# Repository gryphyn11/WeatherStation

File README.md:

# WeatherStation
A weather station powered by a Raspberry Pi front end, and MSP430 series microcontroller back end.

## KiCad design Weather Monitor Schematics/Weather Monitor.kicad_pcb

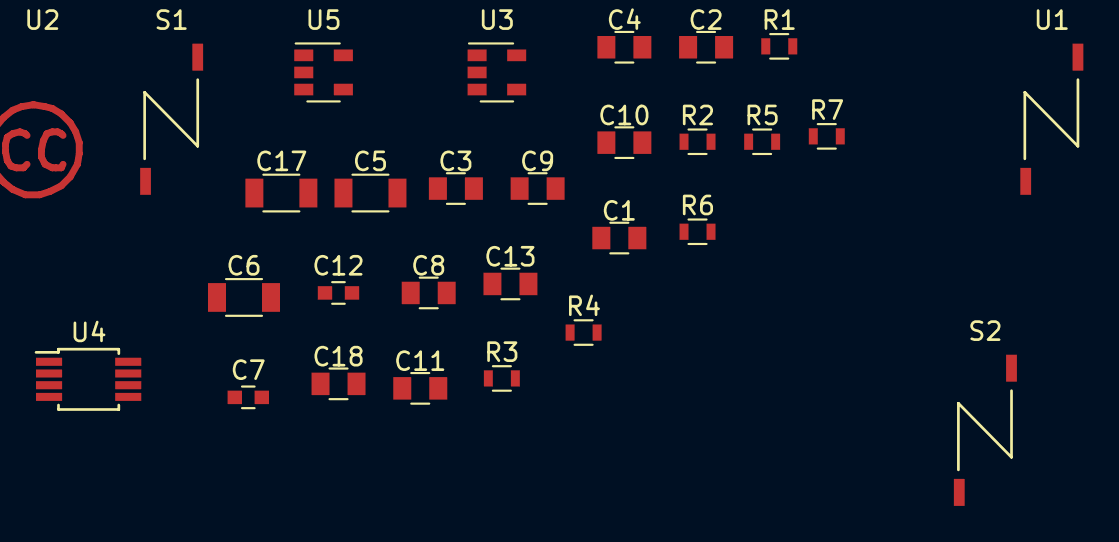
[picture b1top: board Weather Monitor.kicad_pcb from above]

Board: 2 copper layers, 29 parts (0 on the bottom side), 11 nets, no tracks yet.

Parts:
C1, C2, C9, C13: 1.0uF; C_0805
C3, C4, C10, C11: 0.1uF; C_0805
C5, C17: 4.7uF; C_1206
C6: 100nF; C_1206
C7, C12: 0.01uF; C_0603
C8, C18: 2.2uF; C_0805
R1, R2, R3, R4, R5, R6, R7: 4.7k; R_0603
S1, S2: HDC1010; Neosid_Air-Coil_SML_1turn_HDM0131A
U1: MSP430F5659IZQW; Neosid_Air-Coil_SML_1turn_HDM0131A
U2: LPS25HB; Symbol_CreativeCommons_CopperTop_Type2_Small
U3: LP2985-5.0; SOT-23-5
U4: MCP9803_MSOP; MSOP-8_3x3mm_Pitch0.65mm
U5: LP2985-3.3; SOT-23-5

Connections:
/T_P_H_Breakout/SCL_TPH: R7.2, U4.2
/T_P_H_Breakout/SDA_TPH: R6.2, U4.1
/T_P_H_Breakout/TPH_3.3V: C1.2, C3.2, C5.2, C6.1, C11.1, C13.1, C17.1, C18.1, R1.1, R6.1, R7.1, U4.8, U5.5
/T_P_H_Breakout/TPH_5.0V: C8.1, C9.1, C10.1, U3.5, U5.1
/T_P_H_Breakout/TPH_GND: C1.1, C2.2, C3.1, C4.2, C5.1, C6.2, C7.2, C8.2, C9.2, C10.2, C11.2, C12.2, C13.2, C17.2, C18.2, R2.2, R4.1, U3.2, U4.4, U5.2
/T_P_H_Breakout/V_IN_TPH: C2.1, C4.1, U3.1
unnamed: C7.1, U3.4
unnamed: C12.1, U5.4
unnamed: R3.1, U3.3
unnamed: R4.2, U4.5, U4.6, U4.7
unnamed: R5.1, U5.3

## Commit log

2017-11-07 Added current project files
    Added current KiCad project files. Schematics exist for some breakout boards and sensor groups. Some component footprints possibly missing.
